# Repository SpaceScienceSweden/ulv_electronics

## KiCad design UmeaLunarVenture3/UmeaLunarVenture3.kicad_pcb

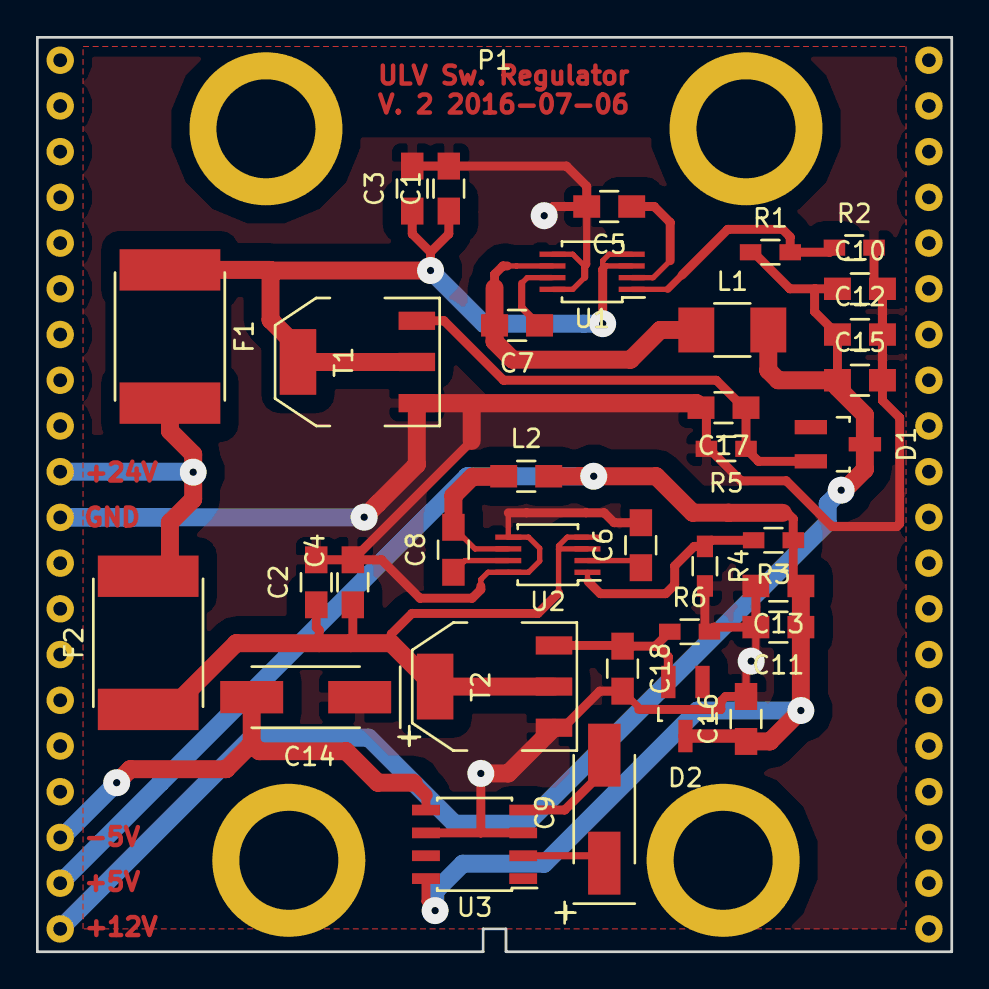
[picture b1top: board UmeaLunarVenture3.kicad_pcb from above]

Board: 2 copper layers, 50.8 x 50.8 mm, 36 parts (0 on the bottom side), 19 nets.

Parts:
C1, C2, C3, C4, C10, C11, C12, C13: 10 uF; C_0805_HandSoldering
C5, C6: 1 uF; C_0805_HandSoldering
C7, C8, C15, C16: 100 nF; C_0805_HandSoldering
C9, C14: 150 uF; TantalC_SizeC_EIA-6032_HandSoldering
C17, C18: 47 nF; C_0805_HandSoldering
D1: ZD +15V; SOT-23_Handsoldering-Swapped_Pads
D2: ZD +5.6V; SOT-23_Handsoldering-Swapped_Pads
F1, F2: Fuse 1.5A; Fuse_SMD2920
L1: 56 uH; C_1210_HandSoldering
L2: 22 uH; C_0805_HandSoldering
P1: SCUBE40; scube40
R1: 140 kOhm; R_0603_HandSoldering
R2, R4: 10 kOhm; R_0603_HandSoldering
R3: 52.3 kOhm; R_0603_HandSoldering
R5, R6: 1k Ohm; R_0603_HandSoldering
T1, T2: T; SOT-223-KAG
U1, U2: MCP16311/2; MSOP-8_3x3mm_Pitch0.65mm_thinpads
U3: MAX660; SOIC-8_3.9x4.9mm_Pitch1.27mm

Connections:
GND: C1.2, C2.2, C3.2, C4.2, C5.2, C6.2, C10.2, C11.2, C12.2, C13.2, C14.1, C15.2, C16.2, C17.2, C18.2, P1.11, R2.2, R4.2, R5.2, R6.2, T1.K, T2.K, U1.5, U1.8, U2.5, U2.8, U3.3, U3.6
unnamed: C1.1, C3.1, F1.1, T1.A, U1.3, U1.4
unnamed: C2.1, C4.1, F2.1, T2.A, U2.3, U2.4
unnamed: C5.1, U1.2
unnamed: C6.1, U2.2
unnamed: C7.1, U1.7
unnamed: C7.2, L1.1, U1.6
unnamed: C8.1, U2.7
unnamed: C8.2, L2.1, U2.6
unnamed: C9.1, U3.2
unnamed: C9.2, U3.4
unnamed: C10.1, C12.1, C15.1, D1.1, L1.2, P1.20, R1.1
unnamed: C11.1, C13.1, C16.1, D2.1, L2.2, P1.19, R3.1, U3.8
unnamed: C14.2, P1.18, U3.5
unnamed: C17.1, D1.2, R5.1, T1.G
unnamed: C18.1, D2.2, R6.1, T2.G
unnamed: F1.2, F2.2, P1.10
unnamed: R1.2, R2.1, U1.1
unnamed: R3.2, R4.1, U2.1

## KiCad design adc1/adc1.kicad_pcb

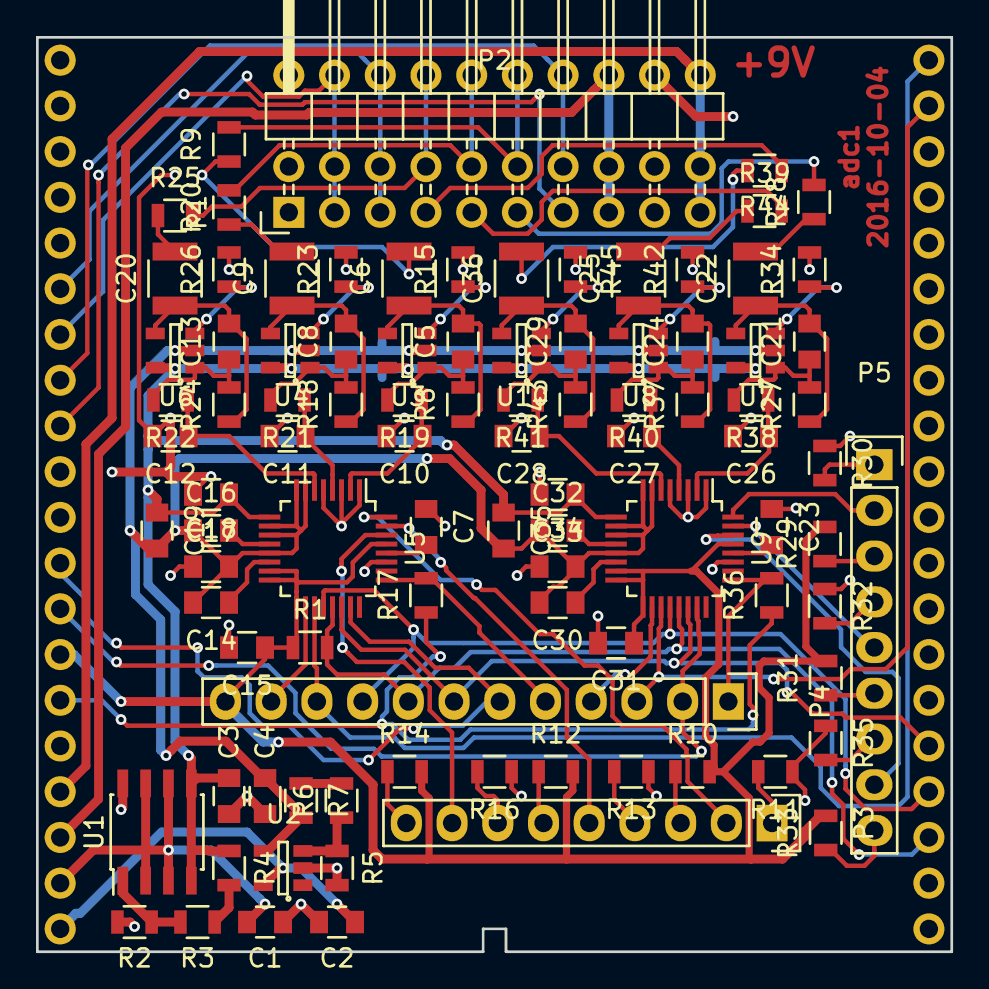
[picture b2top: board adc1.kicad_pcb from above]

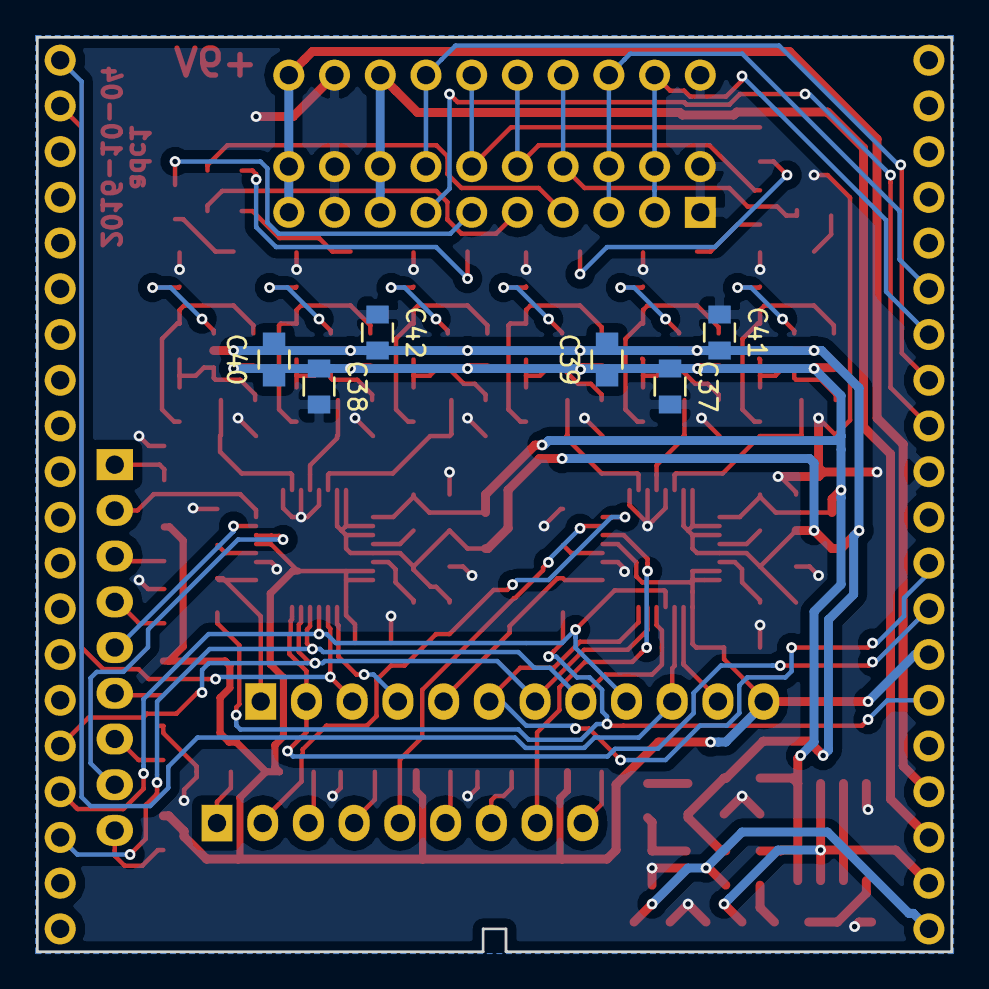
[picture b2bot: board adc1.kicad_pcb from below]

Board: 2 copper layers, 50.8 x 50.8 mm, 102 parts (6 on the bottom side), 88 nets.

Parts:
C1, C2, C37, C38, C39, C40, C41, C42: 100n; C_0805
C3, C4: 10u; C_0805
C5, C8, C13, C21, C24, C29: 1n; C_0805
C6, C9, C20, C22, C25, C36: 220n; C_1210
C7, C14, C15, C16, C17, C18, C19, C23, C30, C31, C32, C33, C34, C35: 1u; C_0805
C10, C11, C12, C26, C27, C28: 18n; C_0805
P1: CONN_02X10; Pin_Header_Angled_2x10_dualfootprint
P2: SCUBE40; scube40_no_holes
P3, P5: CONN_01X09; Pin_Header_Straight_1x09
P4: DEBUG; Pin_Header_Straight_1x12
R1: 100k; R_0805
R2, R3, R5, R6: 10k; R_0805
R4: 660; R_0805
R7: 830; R_0805
R8, R9, R15, R18, R20, R23, R24, R25, R26, R27, R28, R34, R37, R39, R42, R43, R44, R45: 18k; R_0805
R10, R11, R12, R13, R14, R16, R29, R30, R31, R32, R33, R35: 470; R_0805
R17, R36: 50; R_0805
R19, R21, R22, R38, R40, R41: 1k; R_0805
U1: MAX1659; SOIC-8_3.9x4.9mm_Pitch1.27mm
U2: MIC5270YM5-TR; SOT-23-5
U3, U4, U6, U7, U8, U10: LM6211MF; SOT-23-5
U5, U9: ADS131A04; LQFP-32_5x5mm_Pitch0.5mm

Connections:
+2V5: C3.1, C17.1, C19.1, C33.1, C35.1, C37.1, C38.1, C39.1, C40.1, R4.2, U1.4, U1.5, U3.5, U4.5, U5.9, U6.5, U7.5, U8.5, U9.9, U10.5
+3V3: C15.1, C31.1, P2.14, P4.12, R1.1, R10.2, R12.2, R14.2, R29.2, R31.2, R33.2, U5.15, U5.16, U5.17, U5.29, U9.15, U9.16, U9.17, U9.29
+9V: P1.19, P1.20, P2.17
-2V5: C4.1, C14.2, C16.1, C18.2, C19.2, C30.2, C32.1, C34.2, C35.2, C39.2, C40.2, C41.2, C42.2, R7.2, U2.4, U3.2, U4.2, U5.7, U5.8, U5.10, U5.11, U5.13, U6.2, U7.2, U8.2, U9.7, U9.8, U9.10, U9.11, U9.13, U10.2
-9VA: P1.15, P1.16, P2.18
/A0: P1.5, P1.6, P2.6
/A1: P1.3, P1.4, P2.7
/TACHa: P1.14, P2.8
/TACHb: P1.13, P2.9
/channel1//CS: P2.12, P4.6, U5.23
/channel1//DONE: P4.11, U5.18
/channel1//DRDY: P2.40, P4.10, U5.19
/channel1/AIN1: P1.12, R9.2
/channel1/AIN2: P1.10, R20.2
/channel1/AIN3: P1.8, R25.2
/channel1/f_out: P4.5, R17.2, U5.25
/channel2//CS: P2.13, P4.2, U9.23
/channel2//DONE: P4.4, U9.18
/channel2//DRDY: P2.39, P4.3, U9.19
/channel2/AIN1: P1.11, R28.2
/channel2/AIN2: P1.9, R39.2
/channel2/AIN3: P1.7, R44.2
/channel2/f_out: P4.1, R36.2, U9.25
GND: C1.2, C2.1, C3.2, C4.2, C7.1, C10.2, C11.2, C12.2, C15.2, C17.2, C18.1, C23.1, C26.2, C27.2, C28.2, C31.2, C33.2, C34.1, C37.2, C38.2, C41.1, C42.1, P1.1, P1.2, P1.17, P1.18, P2.10, R2.1, R5.1, R11.1, R13.1, R15.2, R16.1, R23.2, R26.2, R30.1, R32.1, R34.2, R35.1, R42.2, R45.2, U1.8, U2.2, U5.1, U5.3, U5.5, U5.27, U9.1, U9.3, U9.5, U9.27
MISO: P2.23, P4.8, R1.2, U5.21, U9.21
MOSI: P2.24, P4.9, U5.20, U9.20
unnamed: C1.1, P2.19, U1.2, U1.3, U1.6, U1.7
unnamed: C2.2, P2.20, U2.5
unnamed: C5.1, R8.2, R19.2, U3.1
unnamed: C5.2, C6.1, R8.1, U3.4
unnamed: C6.2, R9.1
unnamed: C7.2, U5.28
unnamed: C8.1, R18.2, R21.2, U4.1
unnamed: C8.2, C9.1, R18.1, U4.4
unnamed: C9.2, R20.1
unnamed: C10.1, R19.1, U5.2
unnamed: C11.1, R21.1, U5.4
unnamed: C12.1, R22.1, U5.6
unnamed: C13.1, R22.2, R24.2, U6.1
unnamed: C13.2, C20.1, R24.1, U6.4
unnamed: C14.1, U5.14
unnamed: C16.2, U5.12
unnamed: C20.2, R25.1
unnamed: C21.1, R27.2, R38.2, U7.1
unnamed: C21.2, C22.1, R27.1, U7.4
unnamed: C22.2, R28.1
unnamed: C23.2, U9.28
unnamed: C24.1, R37.2, R40.2, U8.1
unnamed: C24.2, C25.1, R37.1, U8.4
unnamed: C25.2, R39.1
unnamed: C26.1, R38.1, U9.2
unnamed: C27.1, R40.1, U9.4
unnamed: C28.1, R41.1, U9.6
unnamed: C29.1, R41.2, R43.2, U10.1
unnamed: C29.2, C36.1, R43.1, U10.4
unnamed: C30.1, U9.14
unnamed: C32.2, U9.12
unnamed: C36.2, R44.1
unnamed: P3.1, R11.2
unnamed: P3.2, U5.32
unnamed: P3.3, R10.1
unnamed: P3.4, R13.2
unnamed: P3.5, U5.31
unnamed: P3.6, R12.1
unnamed: P3.7, R16.2
unnamed: P3.8, U5.30
unnamed: P3.9, R14.1
unnamed: P5.1, R30.2
unnamed: P5.2, U9.32
unnamed: P5.3, R29.1
unnamed: P5.4, R32.2
unnamed: P5.5, U9.31
unnamed: P5.6, R31.1
unnamed: P5.7, R35.2
unnamed: P5.8, U9.30
unnamed: P5.9, R33.1
unnamed: R2.2, R3.1, U1.1
unnamed: R3.2, R4.1
unnamed: R5.2, R6.1, U2.3
unnamed: R6.2, R7.1
unnamed: R15.1, U3.3
unnamed: R23.1, U4.3
unnamed: R26.1, U6.3
unnamed: R34.1, U7.3
unnamed: R42.1, U8.3
unnamed: R45.1, U10.3
SCLK: P2.25, P4.7, U5.22, U9.22
f_ADC: P2.15, R17.1, R36.1

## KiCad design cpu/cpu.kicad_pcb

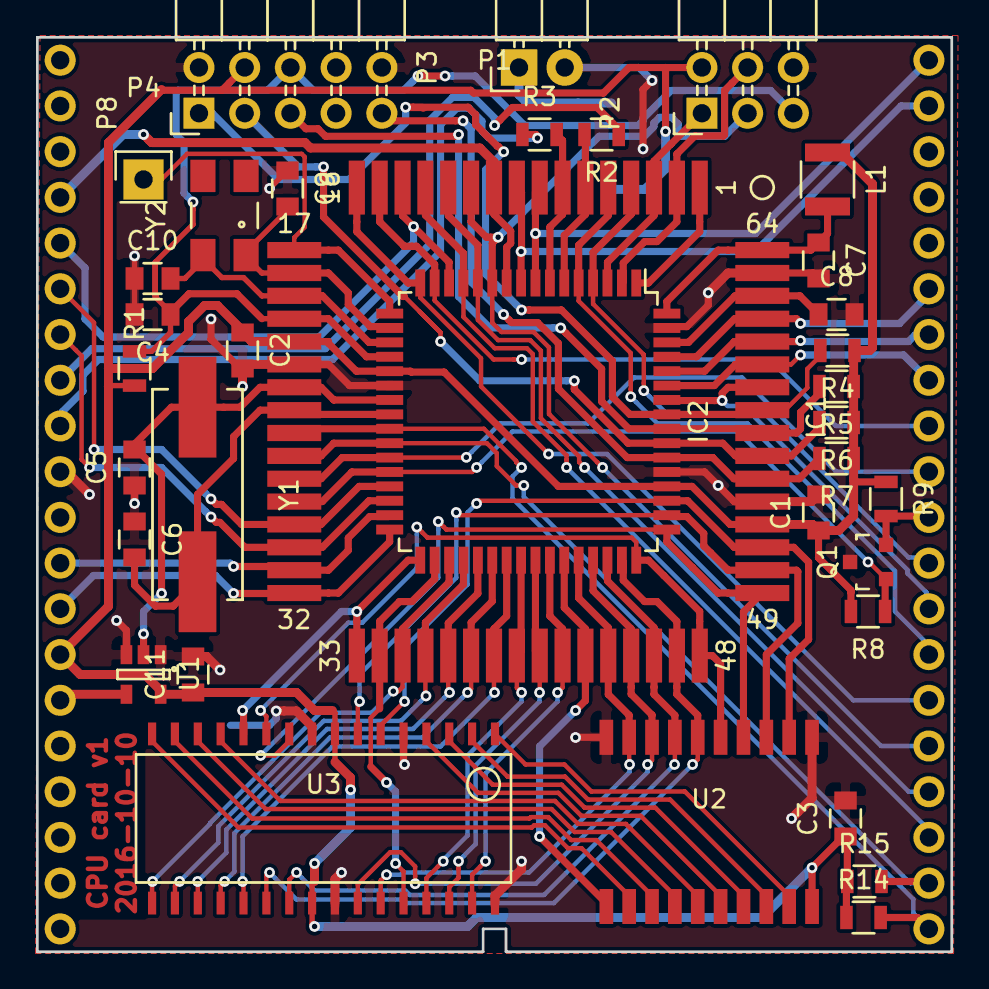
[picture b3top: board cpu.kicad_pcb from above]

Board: 2 copper layers, 50.8 x 50.8 mm, 37 parts (1 on the bottom side), 74 nets.

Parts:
C1, C2, C3, C4, C7, C8, C11: 100n; C_0805
C5, C6: 22p; C_0805
C9, C10: 12p5; C_0805
D1: SMS240; MELF_Standard
IC1: ATMEGA128-A; ATmegaS128
IC2: ATMEGA128-A; TQFP-64_14x14mm_Pitch0.8mm
L1: 10u; C_1210
P1: SCUBE40; scube40_no_holes
P2: ISP; Pin_Header_Angled_2x03
P3: PWR; Pin_Header_Angled_1x02
P4: PWM; Pin_Header_Straight_1x01
P8: JTAG; Pin_Header_Angled_2x05
Q1: NTR4101PT1G; SOT-23
R1, R14, R15: 10k; R_0805
R2, R3, R8: 100k; R_0805
R4, R5, R6, R7: 4k7; R_0805
R9: 3k3; R_0805
U1: 74AHC1G125GW; SOT-23-5
U2: SN74AHC573; SO-20
U3: IS63LV1024; SOJ-32
Y1: 8 MHz; Crystal_HC49-SD_SMD
Y2: 32768 Hz; Crystal_SMD_0603_4Pads

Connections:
+3V3: C1.1, C2.1, C3.1, C11.1, D1.1, IC1.21, IC1.52, IC2.21, IC2.52, L1.1, P1.14, P2.2, P8.4, R1.2, R4.1, R5.1, R6.1, R7.1, R8.2, R9.1, R14.1, R15.1, U1.5, U2.20, U3.8, U3.24
//CS_ADCa: IC1.31, IC2.31, P1.12
//CS_ADCb: IC1.32, IC2.32, P1.13
//DRDYa: IC1.8, IC2.8, P1.40
//DRDYb: IC1.9, IC2.9, P1.39
//RESET: C4.1, IC1.20, IC2.20, P2.5, P8.6, R1.1
/A0: IC1.29, IC2.29, P1.6
/A1: IC1.30, IC2.30, P1.7
/ADC0: IC1.61, IC2.61, P1.35
/ADC1: IC1.60, IC2.60, P1.34
/ADC2: IC1.59, IC2.59, P1.33
/ADC3: IC1.58, IC2.58, P1.29
/AIN0: IC1.4, IC2.4, P1.28
/AIN1: IC1.5, IC2.5, P1.27
/CHANNEL: IC1.14, IC2.14, P1.5
/EN_APWR: IC1.10, IC2.10, P1.4
/LO1: IC1.15, IC2.15, P1.32
/LO2: IC1.16, IC2.16, P1.26
/MISO: IC1.13, IC2.13, P1.23
/MOSI: IC1.12, IC2.12, P1.24
/PDI: IC1.2, IC2.2, P2.4
/PDO: IC1.3, IC2.3, P2.1
/RD: IC1.34, IC2.34, U3.28
/RX: IC1.27, IC2.27, P1.31
/SCL: IC1.25, IC2.25, P1.21, R14.2
/SCLK: IC1.11, IC2.11, P1.25, P2.3
/SDA: IC1.26, IC2.26, P1.22, R15.2
/TACHa: P1.8, R2.1
/TACHb: P1.9, R3.1
/TX: P1.30, Q1.2, R9.2
/WR: IC1.33, IC2.33, U3.12
/f_ADC: P1.15, U1.4
A8: IC1.35, IC2.35, U3.17
A9: IC1.36, IC2.36, U3.18
A10: IC1.37, IC2.37, U3.19
A11: IC1.38, IC2.38, U3.20
A12: IC1.39, IC2.39, U3.21
A13: IC1.40, IC2.40, U3.29
A14: IC1.41, IC2.41, U3.30
A15: IC1.42, IC2.42, U3.31
AD0: IC1.51, IC2.51, U2.2, U3.6
AD1: IC1.50, IC2.50, U2.3, U3.7
AD2: IC1.49, IC2.49, U2.4, U3.10
AD3: IC1.48, IC2.48, U2.5, U3.11
AD4: IC1.47, IC2.47, U2.6, U3.22
AD5: IC1.46, IC2.46, U2.7, U3.23
AD6: IC1.45, IC2.45, U2.8, U3.26
AD7: IC1.44, IC2.44, U2.9, U3.27
ALE: IC1.43, IC2.43, U2.11
GND: C1.2, C2.2, C3.2, C4.2, C5.1, C6.1, C7.2, C8.2, C9.1, C10.1, C11.2, IC1.22, IC1.53, IC1.63, IC2.22, IC2.53, IC2.63, P1.10, P2.6, P3.2, P8.2, P8.10, Q1.3, U1.1, U1.3, U2.1, U2.10, U3.5, U3.9, U3.25, U3.32
unnamed: C5.2, IC1.23, IC2.23, U1.2, Y1.1
unnamed: C6.2, IC1.24, IC2.24, Y1.2
unnamed: C7.1, IC1.64, IC2.64, L1.2
unnamed: C8.1, IC1.62, IC2.62
unnamed: C9.2, IC1.18, IC2.18, Y2.1
unnamed: C10.2, IC1.19, IC2.19, Y2.4
unnamed: D1.2, P3.1
unnamed: IC1.1, IC2.1
unnamed: IC1.6, IC2.6, R2.2
unnamed: IC1.7, IC2.7, R3.2
unnamed: IC1.17, IC2.17, P4.1
unnamed: IC1.28, IC2.28, Q1.1, R8.1
unnamed: IC1.54, IC2.54, P8.9, R7.2
unnamed: IC1.55, IC2.55, P8.3, R6.2
unnamed: IC1.56, IC2.56, P8.5, R5.2
unnamed: IC1.57, IC2.57, P8.1, R4.2
unnamed: U2.12, U3.16
unnamed: U2.13, U3.15
unnamed: U2.14, U3.14
unnamed: U2.15, U3.13
unnamed: U2.16, U3.4
unnamed: U2.17, U3.3
unnamed: U2.18, U3.2
unnamed: U2.19, U3.1

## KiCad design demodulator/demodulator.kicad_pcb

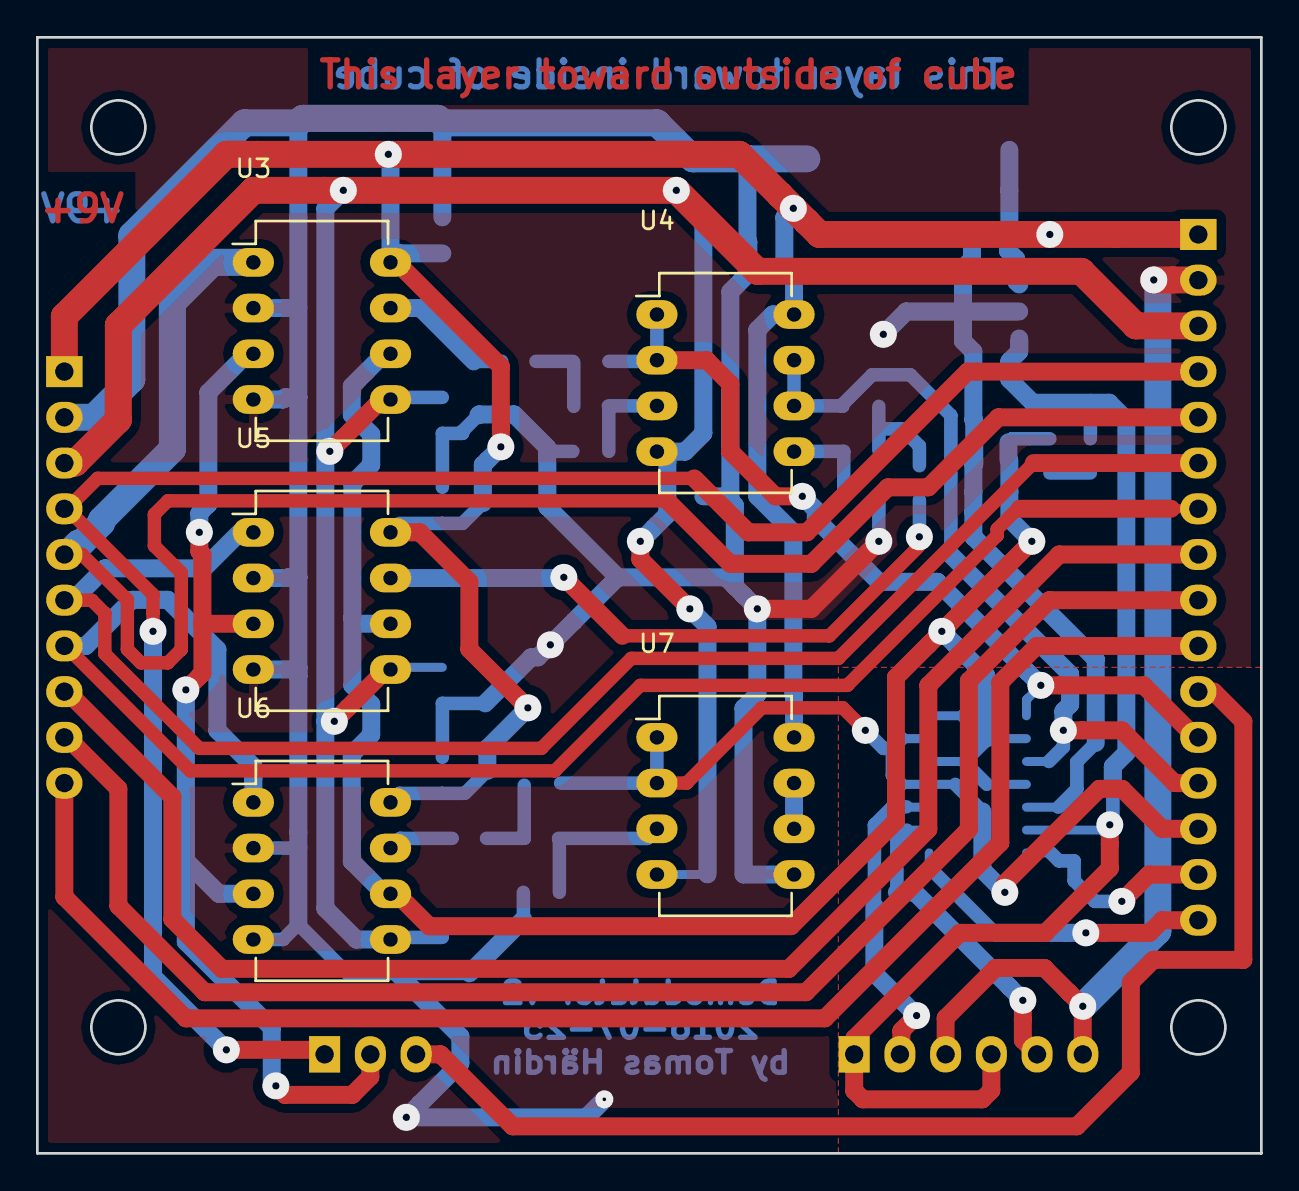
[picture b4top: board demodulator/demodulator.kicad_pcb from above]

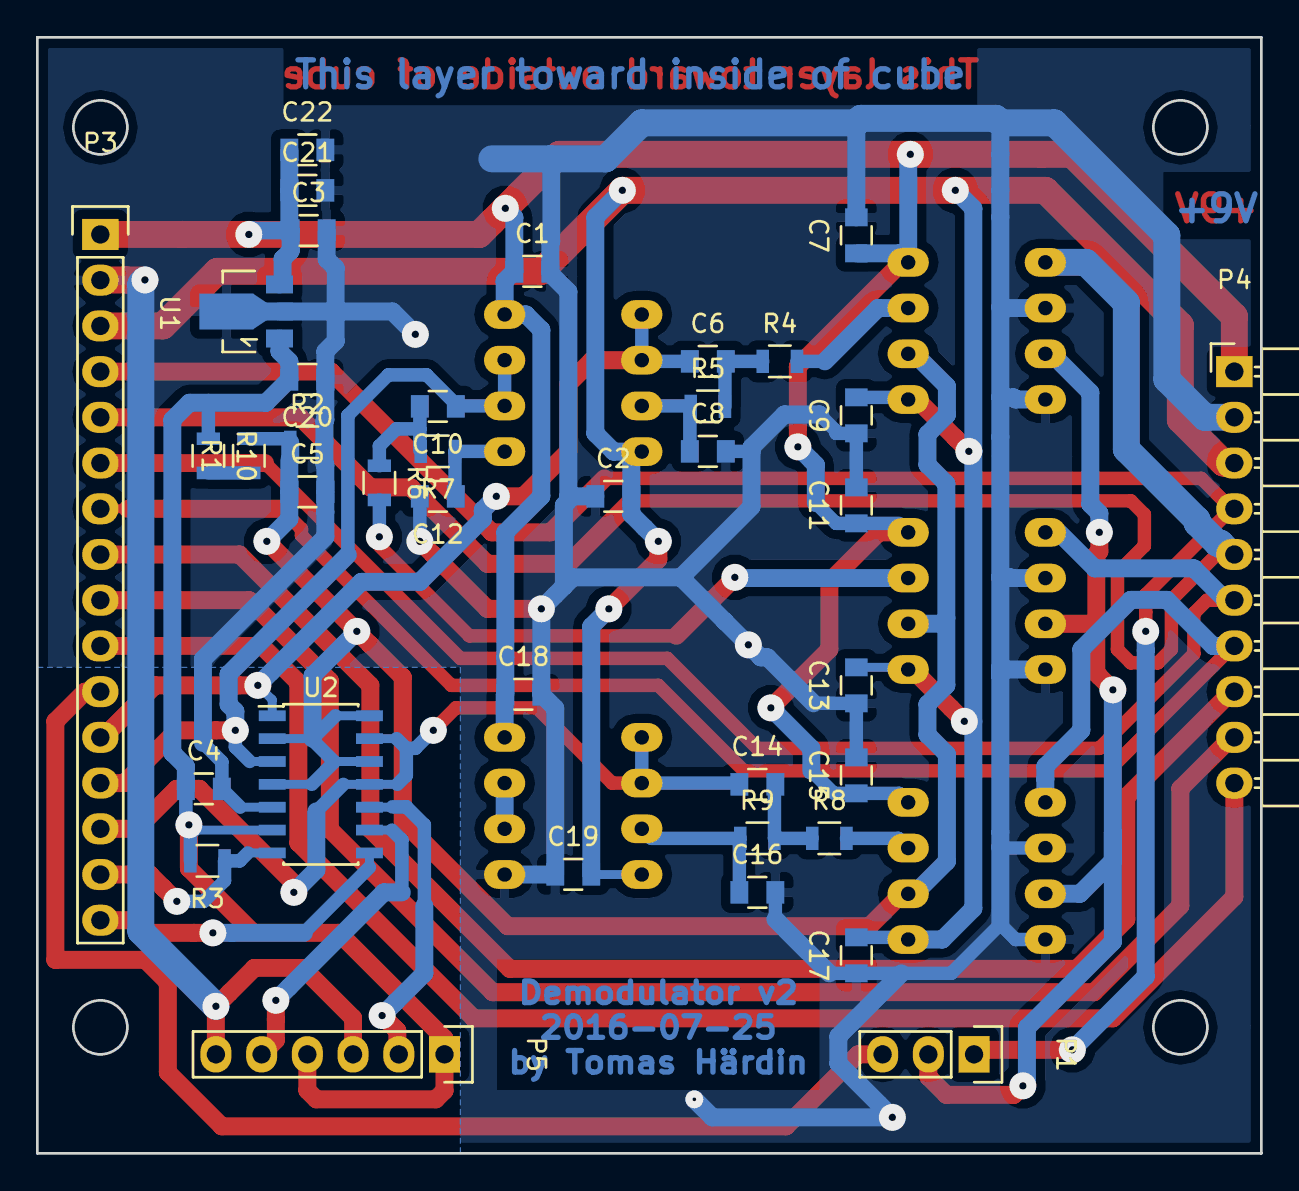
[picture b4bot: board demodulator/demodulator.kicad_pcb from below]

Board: 2 copper layers, 68.0 x 62.0 mm, 43 parts (38 on the bottom side), 32 nets.

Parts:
C1, C2, C3, C4, C5, C7, C9, C11, C13, C15, C17, C18, C19, C20, C21, C22: 100n; C_0805
C6, C8, C10, C12, C14, C16: 1u; C_0805
P1: CONN_01X03; Pin_Header_Straight_1x03
P3: CONN_01X16; Pin_Header_Straight_1x16
P4: CONN_01X10; Pin_Header_Angled_1x10
P5: Adr conf; Pin_Header_Straight_1x06
R1, R2, R3, R10: 10k; R_0805
R4, R5, R6, R7, R8, R9: 100k; R_0805
U1: L78L33; SOT89-3_Housing
U2: MCP3428; SOIC-14_3.9x8.7mm_Pitch1.27mm
U3, U5, U6: AD633; DIP-8_W7.62mm_LongPads
U4, U7: LM6172; DIP-8_W7.62mm_LongPads

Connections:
+3.3VADC: C4.1, C20.2, P5.1, P5.4, R3.2, R10.1, U1.1, U2.6
+9V: C1.1, C3.1, C7.1, C11.1, C15.1, C18.1, C21.1, C22.1, P3.1, P4.1, U1.3, U3.8, U4.8, U5.8, U6.8, U7.8
-9VA: C2.2, C9.2, C13.2, C17.2, C19.2, P3.3, P4.3, U3.5, U4.4, U5.5, U6.5, U7.4
/A0: P3.8, P4.8
/A1: P3.9, P4.9
/LO: P1.3, P3.11
/REF: P3.10, P4.10
/SCL: P3.16, U2.8
/SDA: P3.15, R3.1, U2.7
/TACH: P1.1, P3.4, P4.4
/channel1/BIAS: C5.1, R1.2, R2.1, U2.2, U2.4, U2.12, U2.14, U3.6, U5.6, U6.6
/channel1/DEMOD: C6.1, P3.12, U2.1, U4.1, U4.2
/channel1/X: P3.5, P4.5, U3.1
/channel1/Y: P1.2, U3.3, U5.3, U6.3
/channel2/DEMOD: C10.1, P3.13, U2.3, U4.6, U4.7
/channel2/X: P3.6, P4.6, U5.1
/channel3/DEMOD: C14.1, P3.14, U2.11, U2.13, U7.1, U7.2
/channel3/X: P3.7, P4.7, U6.1
GND: C1.2, C2.1, C3.2, C4.2, C5.2, C7.2, C8.2, C9.1, C11.2, C12.2, C13.1, C15.2, C16.2, C17.1, C18.2, C19.1, C20.1, C21.2, C22.2, P3.2, P4.2, P5.3, P5.6, R2.2, U1.2, U2.5, U3.2, U3.4, U5.2, U5.4, U6.2, U6.4, U7.5
unnamed: C6.2, R4.1, R5.2
unnamed: C8.1, R5.1, U4.3
unnamed: C10.2, R6.1, R7.2
unnamed: C12.1, R7.1, U4.5
unnamed: C14.2, R8.1, R9.2
unnamed: C16.1, R9.1, U7.3
unnamed: P5.2, U2.10
unnamed: P5.5, U2.9
unnamed: R1.1, R10.2
unnamed: R4.2, U3.7
unnamed: R6.2, U5.7
unnamed: R8.2, U6.7
unnamed: U7.6, U7.7

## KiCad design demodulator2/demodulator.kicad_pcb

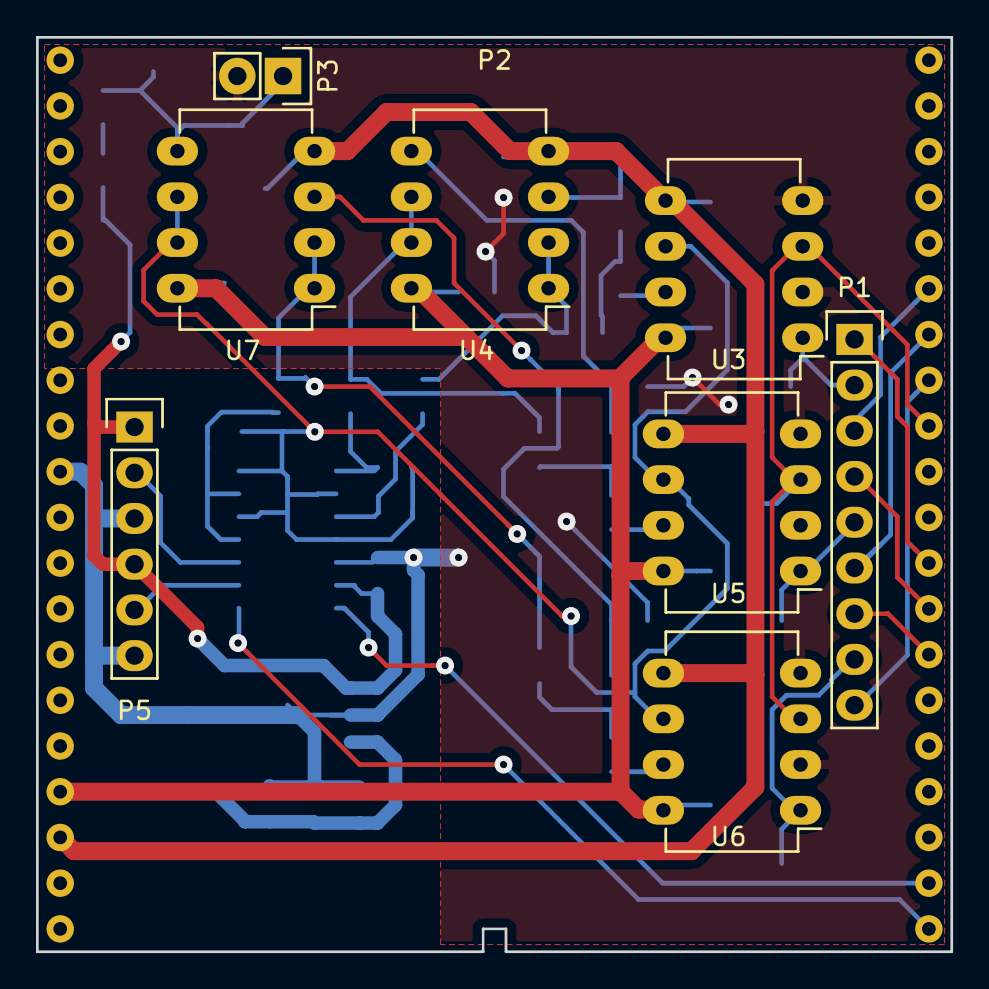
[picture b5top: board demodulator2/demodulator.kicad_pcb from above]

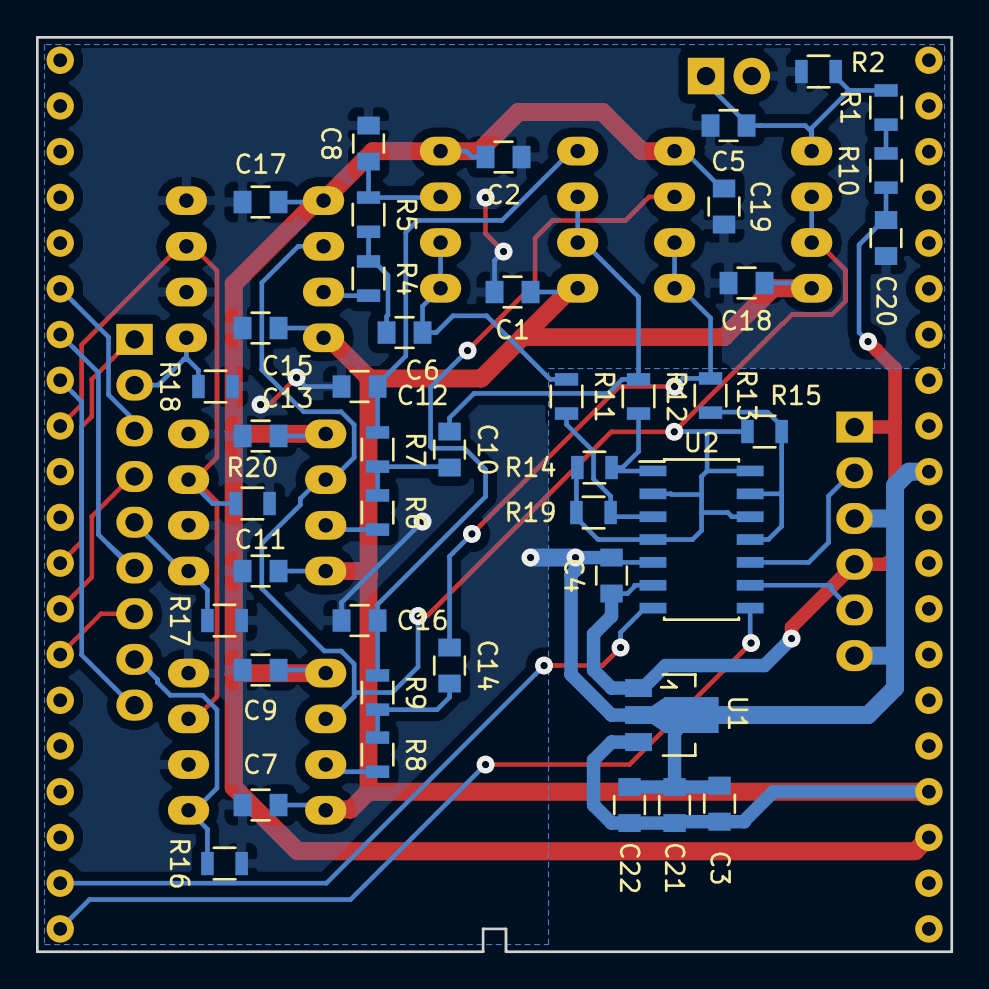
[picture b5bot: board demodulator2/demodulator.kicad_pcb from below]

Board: 2 copper layers, 50.8 x 50.8 mm, 52 parts (43 on the bottom side), 36 nets.

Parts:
C1, C2, C3, C4, C5, C7, C9, C11, C13, C15, C17, C18, C19, C20, C21, C22: 100n; C_0805
C6, C8, C10, C12, C14, C16: 1u; C_0805
P1: CONN_01X09; Pin_Header_Straight_1x09
P2: SCUBE40; scube40_no_holes
P3: ZERO BIAS; Pin_Header_Straight_1x02
P5: Adr conf; Pin_Header_Straight_1x06
R1, R2, R10, R14, R15, R19: 10k; R_0805
R4, R5, R6, R7, R8, R9, R11, R12, R13, R16, R17, R18, R20: 100k; R_0805
U1: L78L33; SOT89-3_Housing
U2: MCP3428; SOIC-14_3.9x8.7mm_Pitch1.27mm
U3, U5, U6: AD633; DIP-8_W7.62mm_LongPads
U4, U7: LM6172; DIP-8_W7.62mm_LongPads

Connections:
+3.3VADC: C4.1, C20.1, P5.1, P5.4, R10.1, U1.1, U2.6
+9V: C1.1, C3.1, C7.1, C11.1, C15.1, C18.1, C21.1, C22.1, P2.17, U1.3, U3.8, U4.8, U5.8, U6.8, U7.8
-9VA: C2.2, C9.2, C13.2, C17.2, C19.2, P2.18, U3.5, U4.4, U5.5, U6.5, U7.4
/SCL: P2.21, U2.8
/SDA: P2.22, U2.7
/channel1/BIAS: R14.1, R15.2, R19.1, U2.2, U2.4, U2.12, U2.14, U3.6, U5.6, U6.6, U7.6, U7.7
/channel1/DEMOD: C6.1, R11.1, U4.1, U4.2
/channel1/X: P1.2, R18.1, U3.1
/channel1/Y: P2.32, R20.1, U3.3, U5.3, U6.3
/channel2/DEMOD: C10.1, R12.1, U4.6, U4.7
/channel2/X: P1.5, R17.1, U5.1
/channel3/DEMOD: C14.1, R13.2, U7.1, U7.2
/channel3/X: P1.8, R16.1, U6.1
GND: C1.2, C2.1, C3.2, C4.2, C5.2, C7.2, C8.2, C9.1, C11.2, C12.2, C13.1, C15.2, C16.2, C17.1, C18.2, C19.1, C20.2, C21.2, C22.2, P2.10, P3.2, P5.3, P5.6, R2.2, R16.2, R17.2, R18.2, R20.2, U1.2, U2.5, U3.2, U3.4, U5.2, U5.4, U6.2, U6.4
unnamed: C5.1, P3.1, R1.2, R2.1, U7.5
unnamed: C6.2, R4.1, R5.2
unnamed: C8.1, R5.1, U4.3
unnamed: C10.2, R6.1, R7.2
unnamed: C12.1, R7.1, U4.5
unnamed: C14.2, R8.1, R9.2
unnamed: C16.1, R9.1, U7.3
unnamed: P1.1, P2.29
unnamed: P1.3, P2.35
unnamed: P1.4, P2.28
unnamed: P1.6, P2.34
unnamed: P1.7, P2.27
unnamed: P1.9, P2.33
unnamed: P5.2, U2.10
unnamed: P5.5, U2.9
unnamed: R1.1, R10.2
unnamed: R4.2, U3.7
unnamed: R6.2, U5.7
unnamed: R8.2, U6.7
unnamed: R11.2, R19.2, U2.3
unnamed: R12.2, R14.2, U2.1
unnamed: R13.1, R15.1, U2.11, U2.13

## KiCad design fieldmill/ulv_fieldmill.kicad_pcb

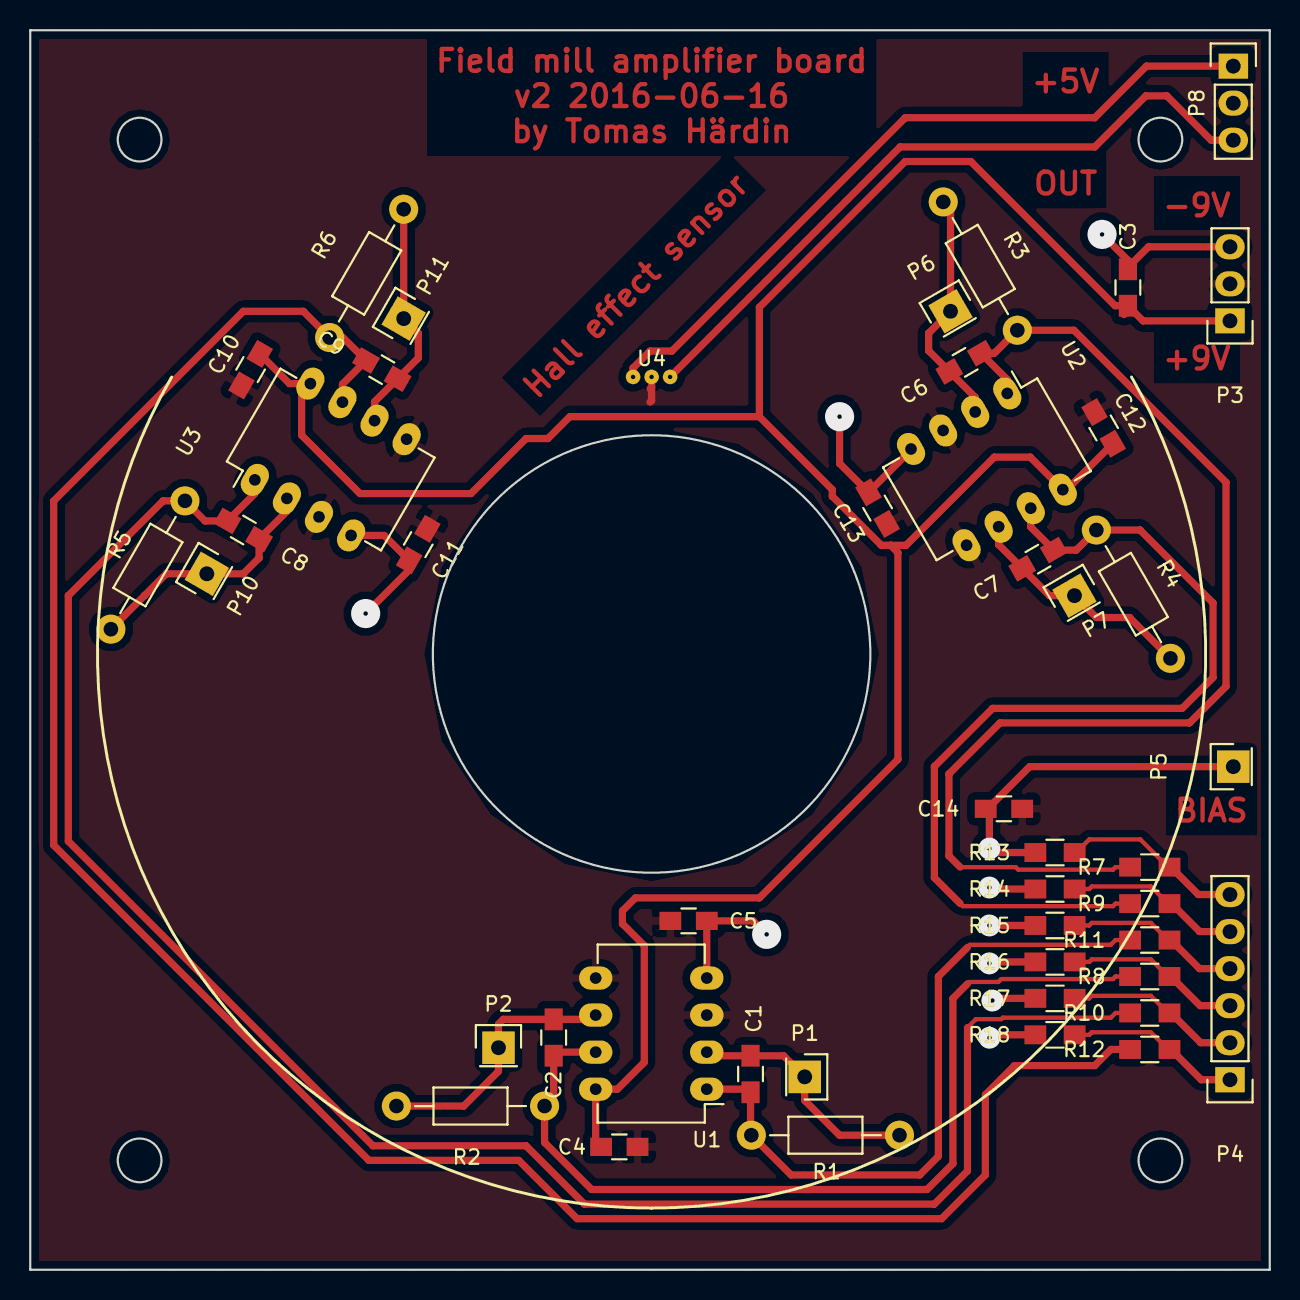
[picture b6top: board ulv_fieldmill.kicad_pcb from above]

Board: 4 copper layers, 85.0 x 85.0 mm, 46 parts (0 on the bottom side), 24 nets.

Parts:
C1, C2, C6, C7, C8, C9: 1p; C_0805_HandSoldering
C3, C14: 1u; C_0805_HandSoldering
C4, C5, C10, C11, C12, C13: 100n; C_0805_HandSoldering
P1, P2, P5, P6, P7, P10, P11: CONN_01X01; Pin_Header_Straight_1x01
P3, P8: CONN_01X03; Pin_Header_Straight_1x03
P4: CONN_01X06; Pin_Header_Straight_1x06
R1, R2, R3, R4, R5, R6: 100M; Resistor_Horizontal_RM10mm
R7, R8, R9, R10, R11, R12, R13, R14, R15, R16, R17, R18: 10k; R_0805_HandSoldering
U1, U2, U3: OPA2604; DIP-8_W7.62mm_LongPads
U4: A3506LU; 3x50mil

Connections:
+5V: P8.1, U4.1
+9VA: C3.2, C4.2, C10.2, C12.2, P3.1, U1.8, U2.8, U3.8
-9VA: C3.1, C5.1, C11.1, C13.1, P3.3, U1.4, U2.4, U3.4
GND: C4.1, C5.2, C10.1, C11.2, C12.1, C13.2, C14.1, P3.2, P8.2, U1.3, U1.5, U2.3, U2.5, U3.3, U3.5, U4.2
unnamed: C1.1, R1.1, R11.2, U1.1
unnamed: C1.2, P1.1, R1.2, U1.2
unnamed: C2.1, R2.1, R8.2, U1.7
unnamed: C2.2, P2.1, R2.2, U1.6
unnamed: C6.1, R3.1, R7.2, U2.1
unnamed: C6.2, P6.1, R3.2, U2.2
unnamed: C7.1, R4.1, R9.2, U2.7
unnamed: C7.2, P7.1, R4.2, U2.6
unnamed: C8.1, R5.1, R10.2, U3.1
unnamed: C8.2, P10.1, R5.2, U3.2
unnamed: C9.1, R6.1, R12.2, U3.7
unnamed: C9.2, P11.1, R6.2, U3.6
unnamed: C14.2, P5.1, R13.2, R14.2, R15.2, R16.2, R17.2, R18.2
unnamed: P4.1, R12.1, R18.1
unnamed: P4.2, R10.1, R17.1
unnamed: P4.3, R8.1, R16.1
unnamed: P4.4, R11.1, R15.1
unnamed: P4.5, R9.1, R14.1
unnamed: P4.6, R7.1, R13.1
unnamed: P8.3, U4.3
